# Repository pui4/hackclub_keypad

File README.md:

# MEGAPAD

MEGAPAD is a macropad that has all the features that you could ever want in a macro pad. Made for Hackclub blueprint. Also I am aware of the weird lines, I don't know what is causing it; I think it is a bug with KiCad.

## FEATURES
MEGAPAD has alot of features so it was difficult to list them all. But I did it anyway:
- 16 clicky* mechanical key switches
- Dual rotary encoders
- An amazing 16 by 16 RGB matrix
- An OLED Display (128x32)
- All powered by a SEEED XIAO RP2040 microcontroller
- Firmware written with KMK
- An IO Expander (not really a feature but I wanted to include it anyway)

*Clickiness not guaranteed

## CAD MODEL
The CAD model consists of two pieces. The base and the top. The PCB is sandwitched between the top and the base. The base includes standoffs built right in. The standoffs require 3 headset inserts (M3x5mx4mm heatset inserts to be specific; the ones you get in the kit). You will also need 3 M3x16mm screws witch also come in the kit.

## PCB
This was my first time using KiCad and making a PCB in general. In retrospect I should have chosen an easier design first but I made this. I know my traces aren't routed the best but as I said it was my first time. The GERBER files are in PCB/jlcpcb/gerber and PCB/jlcpcb/production_files.

## FIRMWARE
The firmware is very bare bones at the minute. I haven't made the macropad yet so I can write anymore detailed firmware. Right now it is based on KMK, however I want to write my own in C++. Because I don't have the hardware I can't test it. When I build it I will update the firmware. It might stay on KMK or it might not we'll see. Also becuase I haven't built it, I have no idea if the firmware works so take that into mind if you wish to build it yourself (you probably shouldn't).

## BOM
- 16x Cherry MX Switches
- 16x Cherry MX Stem Keycaps
- 18x 1N4148 Diodes
- 1x XIAO RP2040
- 2x EC11 Rotary Encoder
- 16x SK6812MINI-E LEDs
- 1x MCP23017
- 1x 0.91" 128x32 OLED Display

Case
- 3x M3x5mx4mm Heatset Inserts
- 3 M3x16mm Screws
- Case Parts (the top and bottom parts)

## REVIEWERS NOTE
I am aware of the board being over the size limit. I am willing to pay for the boards (due to them being too large). Also I can fund the PCB myself I just need the parts from the kit. As for the IO expander I will also provide that myself as I already have one on hand.

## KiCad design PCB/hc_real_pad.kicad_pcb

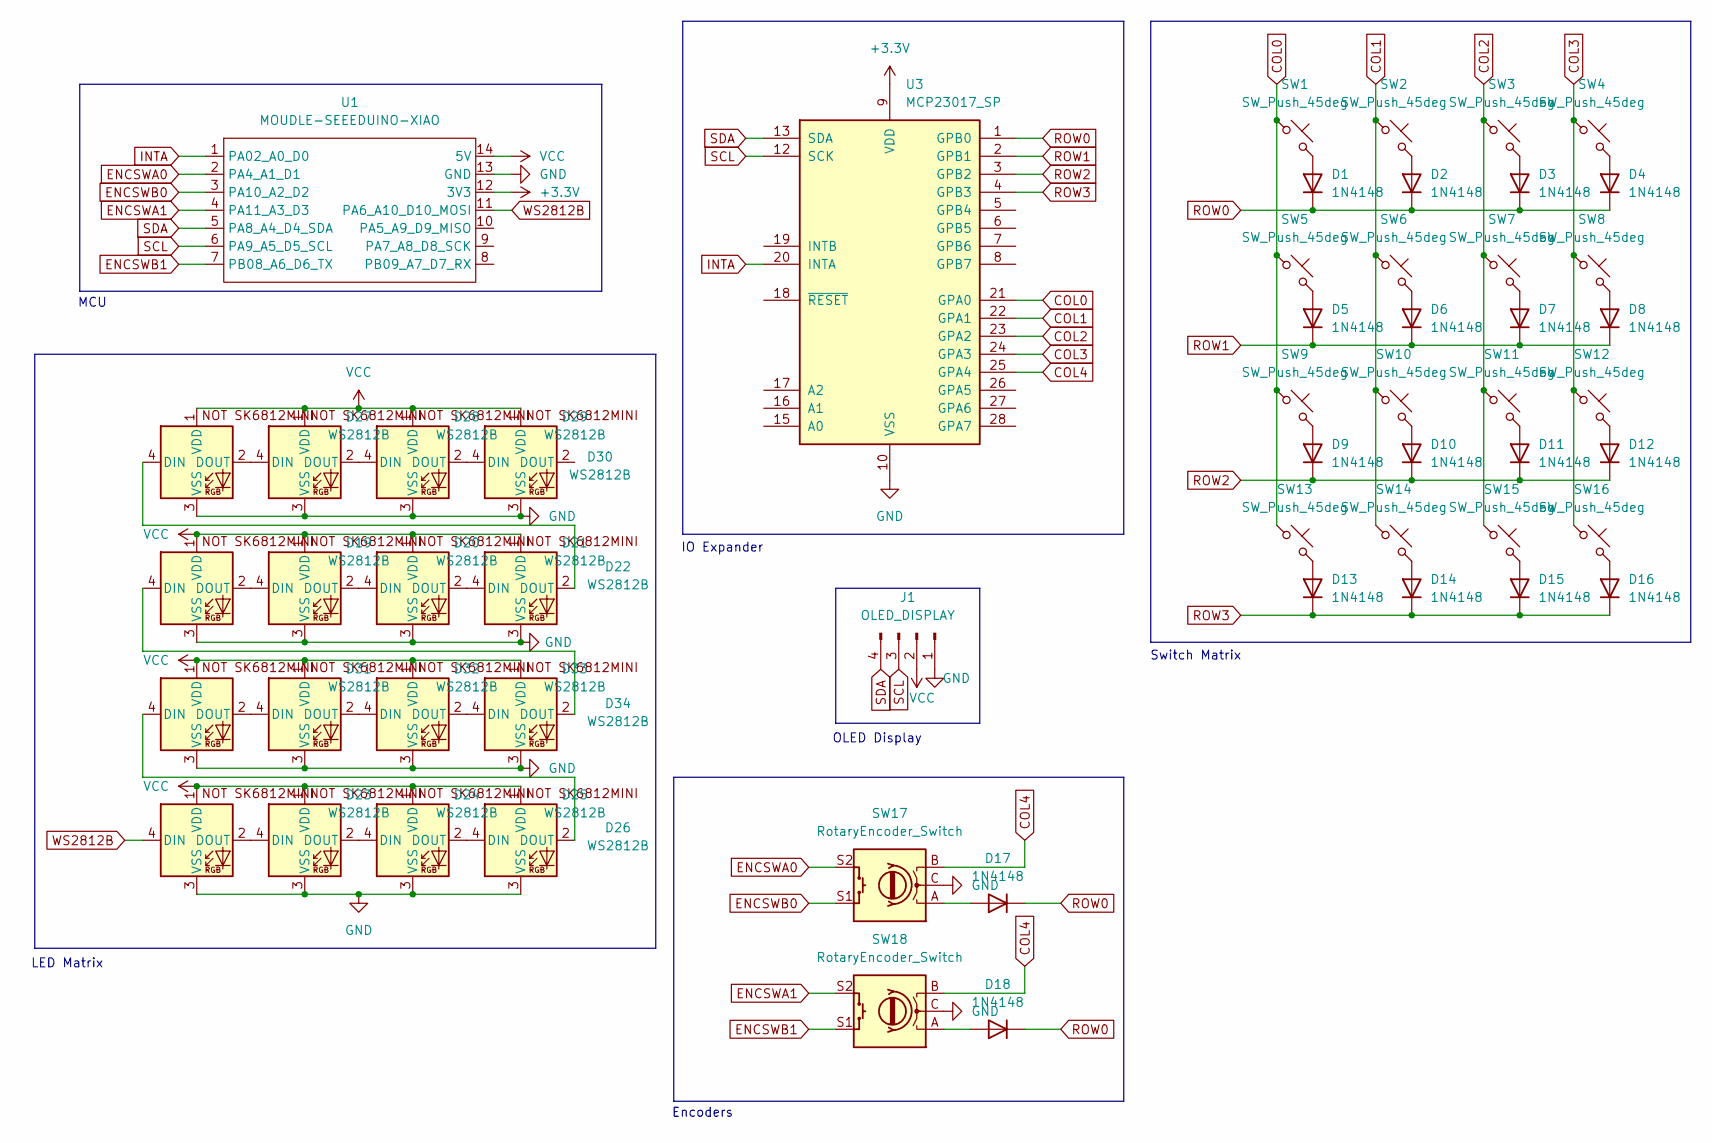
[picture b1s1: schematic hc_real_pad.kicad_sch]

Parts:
D1, D2, D3, D4, D5, D6, D7, D8, D9, D10, D11, D12, D13, D14, D15, D16, D17, D18: 1N4148; D_DO-35_SOD27_P7.62mm_Horizontal
D19, D20, D21, D22, D23, D24, D25, D26, D27, D28, D29, D30, D31, D32, D33, D34: WS2812B; SK6812MINI-E_fixed
J1: OLED_DISPLAY; SSD1306-0.91-OLED-4pin-128x32
SW1, SW2, SW3, SW4, SW5, SW6, SW7, SW8, SW9, SW10, SW11, SW12, SW13, SW14, SW15, SW16: SW_Push_45deg; SW_Cherry_MX_1.00u_PCB
SW17, SW18: RotaryEncoder_Switch; RotaryEncoder_Alps_EC11E-Switch_Vertical_H20mm
U1: MOUDLE-SEEEDUINO-XIAO; XIAO-Generic-Hybrid-14P-2.54-21X17.8MM
U3: MCP23017_SP; DIP-28_W7.62mm

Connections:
+3.3V: U1.12 (3V3), U3.9 (VDD)
COL0: SW1.1, SW5.1, SW9.1, SW13.1, U3.21 (GPA0)
COL1: SW2.1, SW6.1, SW10.1, SW14.1, U3.22 (GPA1)
COL2: SW3.1, SW7.1, SW11.1, SW15.1, U3.23 (GPA2)
COL3: SW4.1, SW8.1, SW12.1, SW16.1, U3.24 (GPA3)
COL4: SW17.B, SW18.B, U3.25 (GPA4)
ENCSWA0: SW17.S2, U1.2 (PA4_A1_D1)
ENCSWA1: SW18.S2, U1.4 (PA11_A3_D3)
ENCSWB0: SW17.S1, U1.3 (PA10_A2_D2)
ENCSWB1: SW18.S1, U1.7 (PB08_A6_D6_TX)
GND: D19.3 (VSS), D20.3 (VSS), D21.3 (VSS), D22.3 (VSS), D23.3 (VSS), D24.3 (VSS), D25.3 (VSS), D26.3 (VSS), D27.3 (VSS), D28.3 (VSS), D29.3 (VSS), D30.3 (VSS), D31.3 (VSS), D32.3 (VSS), D33.3 (VSS), D34.3 (VSS), J1.1, SW17.C, SW18.C, U1.13 (GND), U3.10 (VSS)
INTA: U1.1 (PA02_A0_D0), U3.20 (INTA)
unnamed: D1.2 (A), SW1.2
unnamed: D2.2 (A), SW2.2
unnamed: D3.2 (A), SW3.2
unnamed: D4.2 (A), SW4.2
unnamed: D5.2 (A), SW5.2
unnamed: D6.2 (A), SW6.2
unnamed: D7.2 (A), SW7.2
unnamed: D8.2 (A), SW8.2
unnamed: D9.2 (A), SW9.2
unnamed: D10.2 (A), SW10.2
unnamed: D11.2 (A), SW11.2
unnamed: D12.2 (A), SW12.2
unnamed: D13.2 (A), SW13.2
unnamed: D14.2 (A), SW14.2
unnamed: D15.2 (A), SW15.2
unnamed: D16.2 (A), SW16.2
unnamed: D17.2 (A), SW17.A
unnamed: D18.2 (A), SW18.A
unnamed: D19.4 (DIN), D34.2 (DOUT)
unnamed: D19.2 (DOUT), D20.4 (DIN)
unnamed: D20.2 (DOUT), D21.4 (DIN)
unnamed: D21.2 (DOUT), D22.4 (DIN)
unnamed: D22.2 (DOUT), D27.4 (DIN)
unnamed: D23.2 (DOUT), D24.4 (DIN)
unnamed: D24.2 (DOUT), D25.4 (DIN)
unnamed: D25.2 (DOUT), D26.4 (DIN)
unnamed: D26.2 (DOUT), D31.4 (DIN)
unnamed: D27.2 (DOUT), D28.4 (DIN)
unnamed: D28.2 (DOUT), D29.4 (DIN)
unnamed: D29.2 (DOUT), D30.4 (DIN)
unnamed: D31.2 (DOUT), D32.4 (DIN)
unnamed: D32.2 (DOUT), D33.4 (DIN)
unnamed: D33.2 (DOUT), D34.4 (DIN)
ROW0: D1.1 (K), D2.1 (K), D3.1 (K), D4.1 (K), D17.1 (K), D18.1 (K), U3.1 (GPB0)
ROW1: D5.1 (K), D6.1 (K), D7.1 (K), D8.1 (K), U3.2 (GPB1)
ROW2: D9.1 (K), D10.1 (K), D11.1 (K), D12.1 (K), U3.3 (GPB2)
ROW3: D13.1 (K), D14.1 (K), D15.1 (K), D16.1 (K), U3.4 (GPB3)
SCL: J1.3, U1.6 (PA9_A5_D5_SCL), U3.12 (SCK)
SDA: J1.4, U1.5 (PA8_A4_D4_SDA), U3.13 (SDA)
VCC: D19.1 (VDD), D20.1 (VDD), D21.1 (VDD), D22.1 (VDD), D23.1 (VDD), D24.1 (VDD), D25.1 (VDD), D26.1 (VDD), D27.1 (VDD), D28.1 (VDD), D29.1 (VDD), D30.1 (VDD), D31.1 (VDD), D32.1 (VDD), D33.1 (VDD), D34.1 (VDD), J1.2, U1.14 (5V)
WS2812B: D23.4 (DIN), U1.11 (PA6_A10_D10_MOSI)

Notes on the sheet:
LED Matrix
IO Expander
Encoders
MCU
Switch Matrix
OLED Display

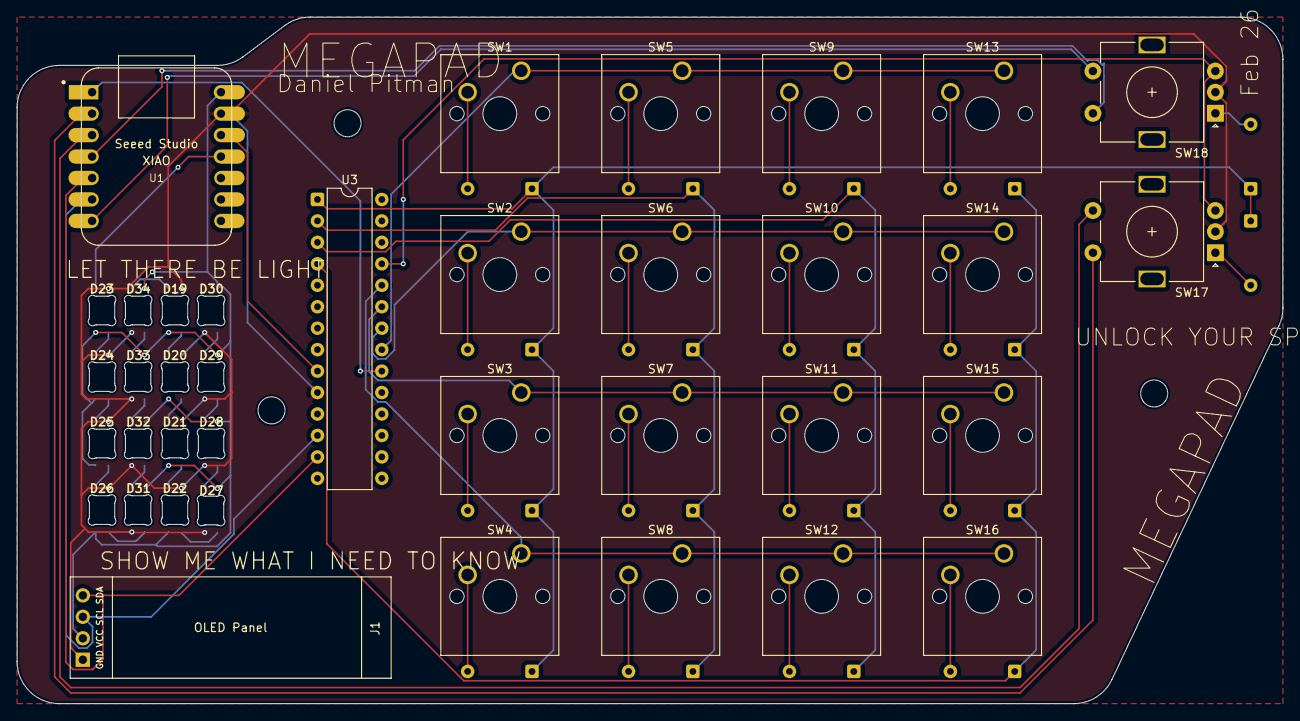
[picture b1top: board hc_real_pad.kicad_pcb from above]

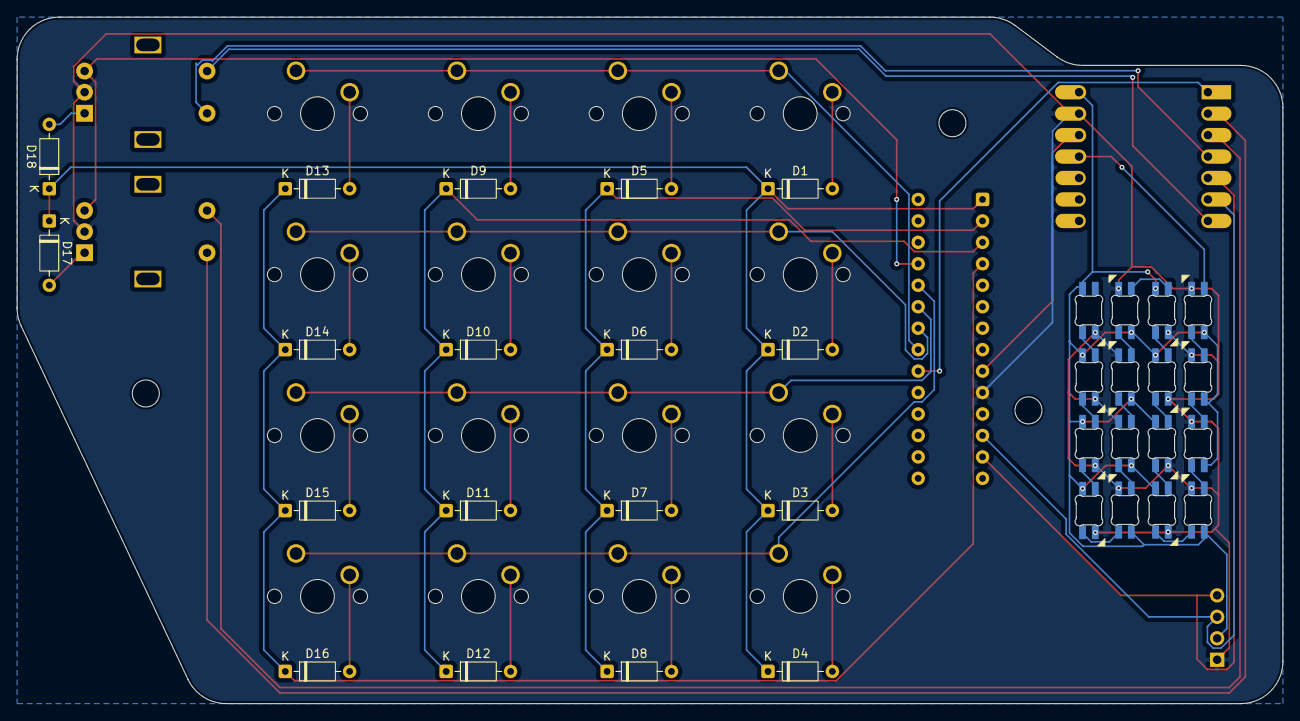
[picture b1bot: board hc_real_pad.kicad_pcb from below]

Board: 2 copper layers, 149.8 x 81.2 mm, 55 parts (18 on the bottom side), 53 nets.

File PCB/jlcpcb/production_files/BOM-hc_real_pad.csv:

Comment,Designator,Footprint,LCSC,Quantity
SW_Push_45deg,SW14,SW_Cherry_MX_1.00u_PCB,,1
SW_Push_45deg,SW2,SW_Cherry_MX_1.00u_PCB,,1
RotaryEncoder_Switch,SW18,RotaryEncoder_Alps_EC11E-Switch_Vertical_H20mm,,1
WS2812B,D21,SK6812MINI-E_fixed,,1
WS2812B,D25,SK6812MINI-E_fixed,,1
SW_Push_45deg,SW4,SW_Cherry_MX_1.00u_PCB,,1
WS2812B,D26,SK6812MINI-E_fixed,,1
SW_Push_45deg,SW11,SW_Cherry_MX_1.00u_PCB,,1
WS2812B,D31,SK6812MINI-E_fixed,,1
WS2812B,D23,SK6812MINI-E_fixed,,1
SW_Push_45deg,SW1,SW_Cherry_MX_1.00u_PCB,,1
SW_Push_45deg,SW6,SW_Cherry_MX_1.00u_PCB,,1
WS2812B,D34,SK6812MINI-E_fixed,,1
WS2812B,D27,SK6812MINI-E_fixed,,1
SW_Push_45deg,SW8,SW_Cherry_MX_1.00u_PCB,,1
SW_Push_45deg,SW9,SW_Cherry_MX_1.00u_PCB,,1
RotaryEncoder_Switch,SW17,RotaryEncoder_Alps_EC11E-Switch_Vertical_H20mm,,1
WS2812B,D33,SK6812MINI-E_fixed,,1
WS2812B,D32,SK6812MINI-E_fixed,,1
SW_Push_45deg,SW3,SW_Cherry_MX_1.00u_PCB,,1
SW_Push_45deg,SW5,SW_Cherry_MX_1.00u_PCB,,1
WS2812B,D24,SK6812MINI-E_fixed,,1
SW_Push_45deg,SW12,SW_Cherry_MX_1.00u_PCB,,1
MOUDLE-SEEEDUINO-XIAO,U1,XIAO-Generic-Hybrid-14P-2.54-21X17.8MM,,1
WS2812B,D29,SK6812MINI-E_fixed,,1
SW_Push_45deg,SW15,SW_Cherry_MX_1.00u_PCB,,1
SW_Push_45deg,SW16,SW_Cherry_MX_1.00u_PCB,,1
WS2812B,D30,SK6812MINI-E_fixed,,1
MCP23017_SP,U3,DIP-28_W7.62mm,,1
OLED_DISPLAY,J1,SSD1306-0.91-OLED-4pin-128x32,,1
WS2812B,D28,SK6812MINI-E_fixed,,1
SW_Push_45deg,SW10,SW_Cherry_MX_1.00u_PCB,,1
WS2812B,D19,SK6812MINI-E_fixed,,1
SW_Push_45deg,SW13,SW_Cherry_MX_1.00u_PCB,,1
SW_Push_45deg,SW7,SW_Cherry_MX_1.00u_PCB,,1
WS2812B,D22,SK6812MINI-E_fixed,,1
WS2812B,D20,SK6812MINI-E_fixed,,1
1N4148,D11,D_DO-35_SOD27_P7.62mm_Horizontal,,1
1N4148,D4,D_DO-35_SOD27_P7.62mm_Horizontal,,1
1N4148,D9,D_DO-35_SOD27_P7.62mm_Horizontal,,1
1N4148,D14,D_DO-35_SOD27_P7.62mm_Horizontal,,1
1N4148,D17,D_DO-35_SOD27_P7.62mm_Horizontal,,1
1N4148,D7,D_DO-35_SOD27_P7.62mm_Horizontal,,1
1N4148,D6,D_DO-35_SOD27_P7.62mm_Horizontal,,1
1N4148,D10,D_DO-35_SOD27_P7.62mm_Horizontal,,1
1N4148,D13,D_DO-35_SOD27_P7.62mm_Horizontal,,1
1N4148,D16,D_DO-35_SOD27_P7.62mm_Horizontal,,1
1N4148,D1,D_DO-35_SOD27_P7.62mm_Horizontal,,1
1N4148,D8,D_DO-35_SOD27_P7.62mm_Horizontal,,1
1N4148,D5,D_DO-35_SOD27_P7.62mm_Horizontal,,1
1N4148,D12,D_DO-35_SOD27_P7.62mm_Horizontal,,1
1N4148,D2,D_DO-35_SOD27_P7.62mm_Horizontal,,1
1N4148,D18,D_DO-35_SOD27_P7.62mm_Horizontal,,1
1N4148,D3,D_DO-35_SOD27_P7.62mm_Horizontal,,1
1N4148,D15,D_DO-35_SOD27_P7.62mm_Horizontal,,1

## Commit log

2026-02-15 first commit (made the project)
2026-02-15 did schematic
2026-02-15 fixed issues with schematic
2026-02-16 wired up the matrix
2026-02-16 finished making the pcb
2026-02-16 Reorganised folder structure
2026-02-16 fixed the screw holes
2026-02-16 made the model for the case
2026-02-16 wrote the firmware
2026-02-16 Add README
2026-02-16 added images
2026-02-16 added the models in properly
2026-02-16 fixed the features
2026-02-18 added assembly and updated readme
2026-02-18 added gerber files
2026-02-18 added gerbers to readme
2026-02-18 added ground planes
2026-03-18 fixed plate alignment
2026-03-26 updated the models due to clearance issues
